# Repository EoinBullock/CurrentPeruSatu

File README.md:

# CurrentPeruSatu
hw plugin pcb for current measurement

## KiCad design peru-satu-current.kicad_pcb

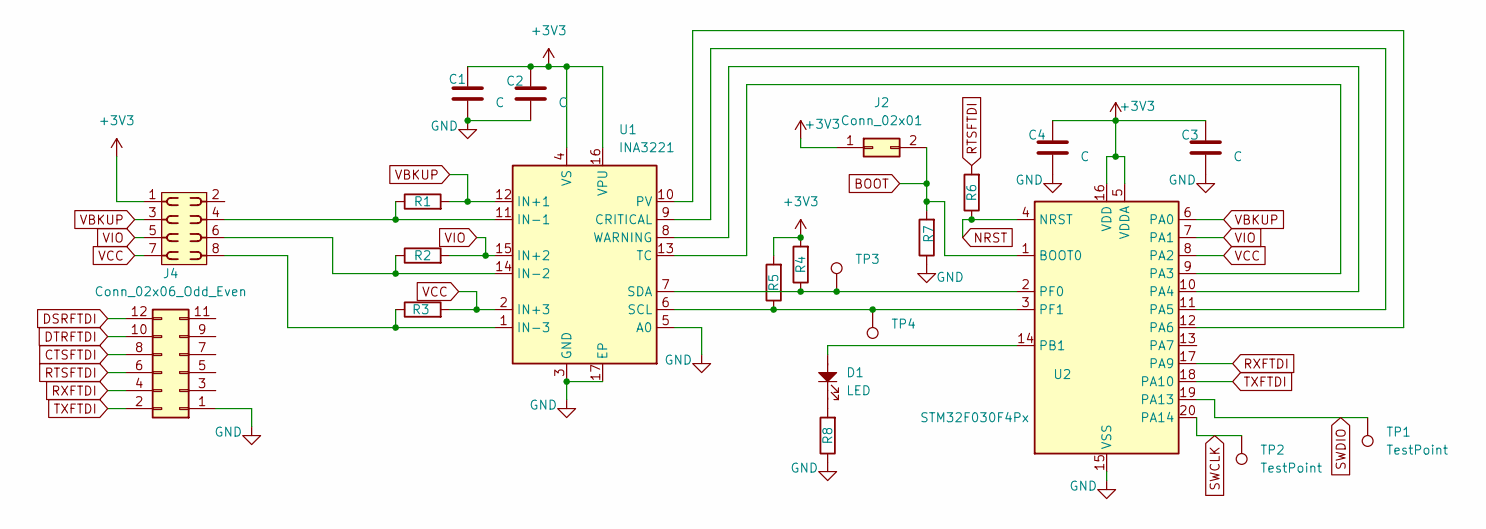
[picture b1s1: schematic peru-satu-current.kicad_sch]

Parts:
C1, C3: C; C_0603_1608Metric
C2, C4: C; C_0402_1005Metric
D1: LED; LED_0603_1608Metric
J1: PINHD_2x4_Female; PinSocket_2x04_P2.54mm_Vertical
J2: Conn_02x01; PinHeader_1x02_P2.54mm_Vertical
J4: Conn_02x06_Odd_Even; PinSocket_2x06_P2.54mm_Vertical
R1, R2, R3: R; R_0603_1608Metric
R4, R5, R6, R7: 4.7k; R_0402_1005Metric
R8: 470R; R_0402_1005Metric
TP1, TP2: TestPoint; TestPoint_THTPad_2.0x2.0mm_Drill1.0mm
TP3, TP4: TestPoint; TestPoint_Pad_1.0x1.0mm
U1: INA3221; Texas_RGV0016A_VQFN-16-1EP_4x4mm_P0.65mm_EP2.1x2.1mm
U2: STM32F030F4Px; TSSOP-20_4.4x6.5mm_P0.65mm

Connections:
+3V3: C1.1, C2.1, C3.1, C4.1, J1.1, J2.1, R4.2, R5.2, U1.4 (VS), U1.16 (VPU), U2.5 (VDDA), U2.16 (VDD)
BOOT: J2.2, R7.2, U2.1 (BOOT0)
CTSFTDI: J4.8
DSRFTDI: J4.12
DTRFTDI: J4.10
GND: C1.2, C2.2, C3.2, C4.2, J4.1, R7.1, R8.1, U1.3 (GND), U1.5 (A0), U1.17 (EP), U2.15 (VSS)
NRST: R6.1, U2.4 (NRST)
unnamed: D1.1, R8.2
unnamed: U1.9 (CRITICAL), U2.11 (PA5)
unnamed: J1.4, R1.1, U1.11 (IN-1)
unnamed: J1.6, R2.1, U1.14 (IN-2)
unnamed: J1.8, R3.1, U1.1 (IN-3)
unnamed: U1.10 (PV), U2.12 (PA6)
unnamed: R5.1, TP4.1, U1.6 (SCL), U2.3 (PF1)
unnamed: R4.1, TP3.1, U1.7 (SDA), U2.2 (PF0)
unnamed: U1.13 (TC), U2.9 (PA3)
unnamed: U1.8 (WARNING), U2.10 (PA4)
unnamed: D1.2, U2.14 (PB1)
RTSFTDI: J4.6, R6.2
RXFTDI: J4.4, U2.17 (PA9)
SWCLK: TP2.1, U2.20 (PA14)
SWDIO: TP1.1, U2.19 (PA13)
TXFTDI: J4.2, U2.18 (PA10)
VBKUP: J1.3, R1.2, U1.12 (IN+1), U2.6 (PA0)
VCC: J1.7, R3.2, U1.2 (IN+3), U2.8 (PA2)
VIO: J1.5, R2.2, U1.15 (IN+2), U2.7 (PA1)

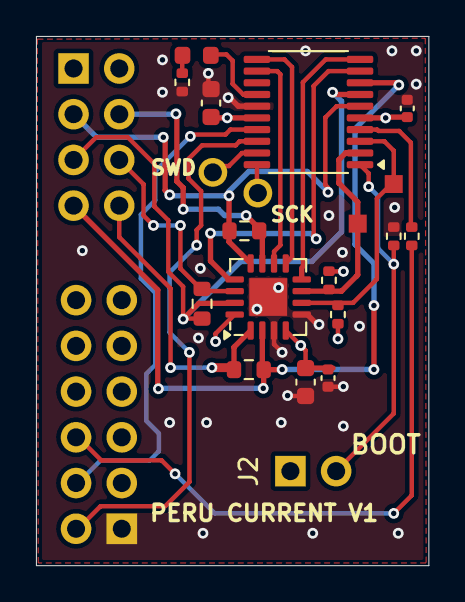
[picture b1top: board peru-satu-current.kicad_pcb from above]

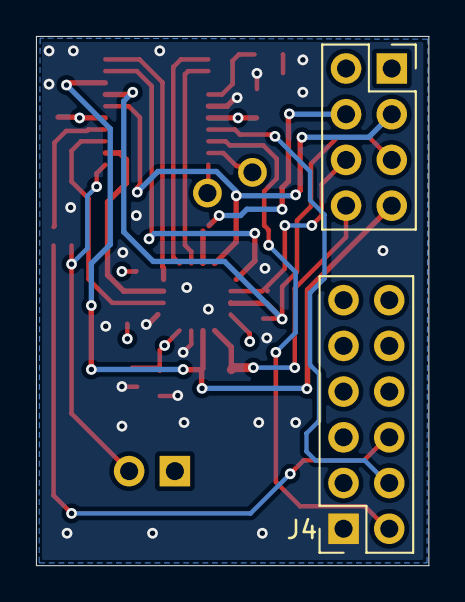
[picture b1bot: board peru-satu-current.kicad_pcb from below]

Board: 4 copper layers, 21.8 x 29.4 mm, 22 parts (2 on the bottom side), 23 nets.
